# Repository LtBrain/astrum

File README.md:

# **ASTRUM**
  
Astrum is a full robot designed for Science Olympiad's Robot Tour Event (2025-2026). It is designed to follow a predetermined path to navigate a maze and manipulate a water bottle to specific points on the floor. It is equipped with dual GA25 motors, a controller board (Aero), wheel encoders and an IMU to keep track of orientation. These features allow Astrum to quickly navigate the predetermined path efficiently and accurately with a PID loop controlling robot turning and motor speed.  
<br><br>
Astrum was created for the purpose of "placing" at the Mid-Hudson Valley Regionals competition, and to secure Nanuet a medal. Additionally, it serves as an educational tool for other students interested in robotics and control systems. It is able to be programmed in C, as well as Arduino, making it very effective for learning embedded software. This is also practice for myself, testing my design skills with both the hardware, and efficiently programming software to run on said board.  
  
## PCB

## Wiring Diagram 

## BOM
Here's the BOM:  

 |Item #|Name                                       |Link                                     |Amount               |Cost   |
|------|-------------------------------------------|-----------------------------------------|---------------------|-------|
|1     |PCB + Assembly + Shipping                  |jlcpcb.com                               |1 order (2 boards)   |$170.40|
|2     |25GA-370 Brushed Motors                    |https://www.aliexpress.us/item/3256807346702379.html?|2                    |$12.94 |
|3     |Alinan AS5600 Encoder Boards               |https://www.aliexpress.us/item/3256809413529733.html?                              |1 pack (5 Encoders)  |$6.09 |
|4     |STEMMA QT to Male Header Cable             |https://www.aliexpress.com/item/3256805529535394.html?    |2                    |$2.78 |
|5     |2800 mAh AA NIMH Batteries                 |https://www.aliexpress.com/item/3256808440628751.html?                     |1 pack (12 Batteries)|$7.67 |
|6     |4 x AA Battery Holder                      |https://www.aliexpress.com/item/2255799895517935.html?     |2                    |$1.90  |
|7     |M3 16mm SHCS                               |M3 SHCS link                             |50                   |Paid by me  |
|8     |BaneBots T6 Wheel, 2-3/8" x 0.6", Hub Mount|https://banebots.com/t61p-242bp/         |2                    |$6.60  |
|9     |MF128ZZ Bearings - 8mm x 12mm x 3.5mm      |https://www.aliexpress.com/item/3256807566213882.html?                      |1 pack (8 bearings) |$6.10  |
|10    |Polulu 1/2 Inch Metal Ball Caster Wheels   |https://www.aliexpress.com/item/3256808387820251.html?     |4                    |$4.63 |
|11    |Pin Headers                                |https://www.aliexpress.com/item/2255800801798474.html?    |10                    |$1.69  |
|      |                                           |                                         |                     |Total: |
|      |                                           |                                         |                     |$220.80|
 
https://github.com/LtBrain/astrum/blob/main/Astrum%20BOM%20-%20Sheet1.csv

This covers the total sum of all the major parts.  

There is a more in depth BOM for the PCB assembly components itself: [BOM-astrum-JLCPCB Assembly Order.xls](https://github.com/user-attachments/files/23870804/BOM-astrum-JLCPCB.Assembly.Order.xls)  
  
REVIEWERS: Do note that I am aware of the high PCB fabrication costs + shipping, but this is the cheapest I could find it for (at JLCPCB). Additionally, the global standard direct shipping option will not work for this board. Sadly, JLCPCB requires the purchase to be under 59.99 dollars, which this board exceeds. This is why it got so expensive. Also do note that I have optimized my BOMs to be as cheap as possible to lower the amount of money spent by Hackclub.

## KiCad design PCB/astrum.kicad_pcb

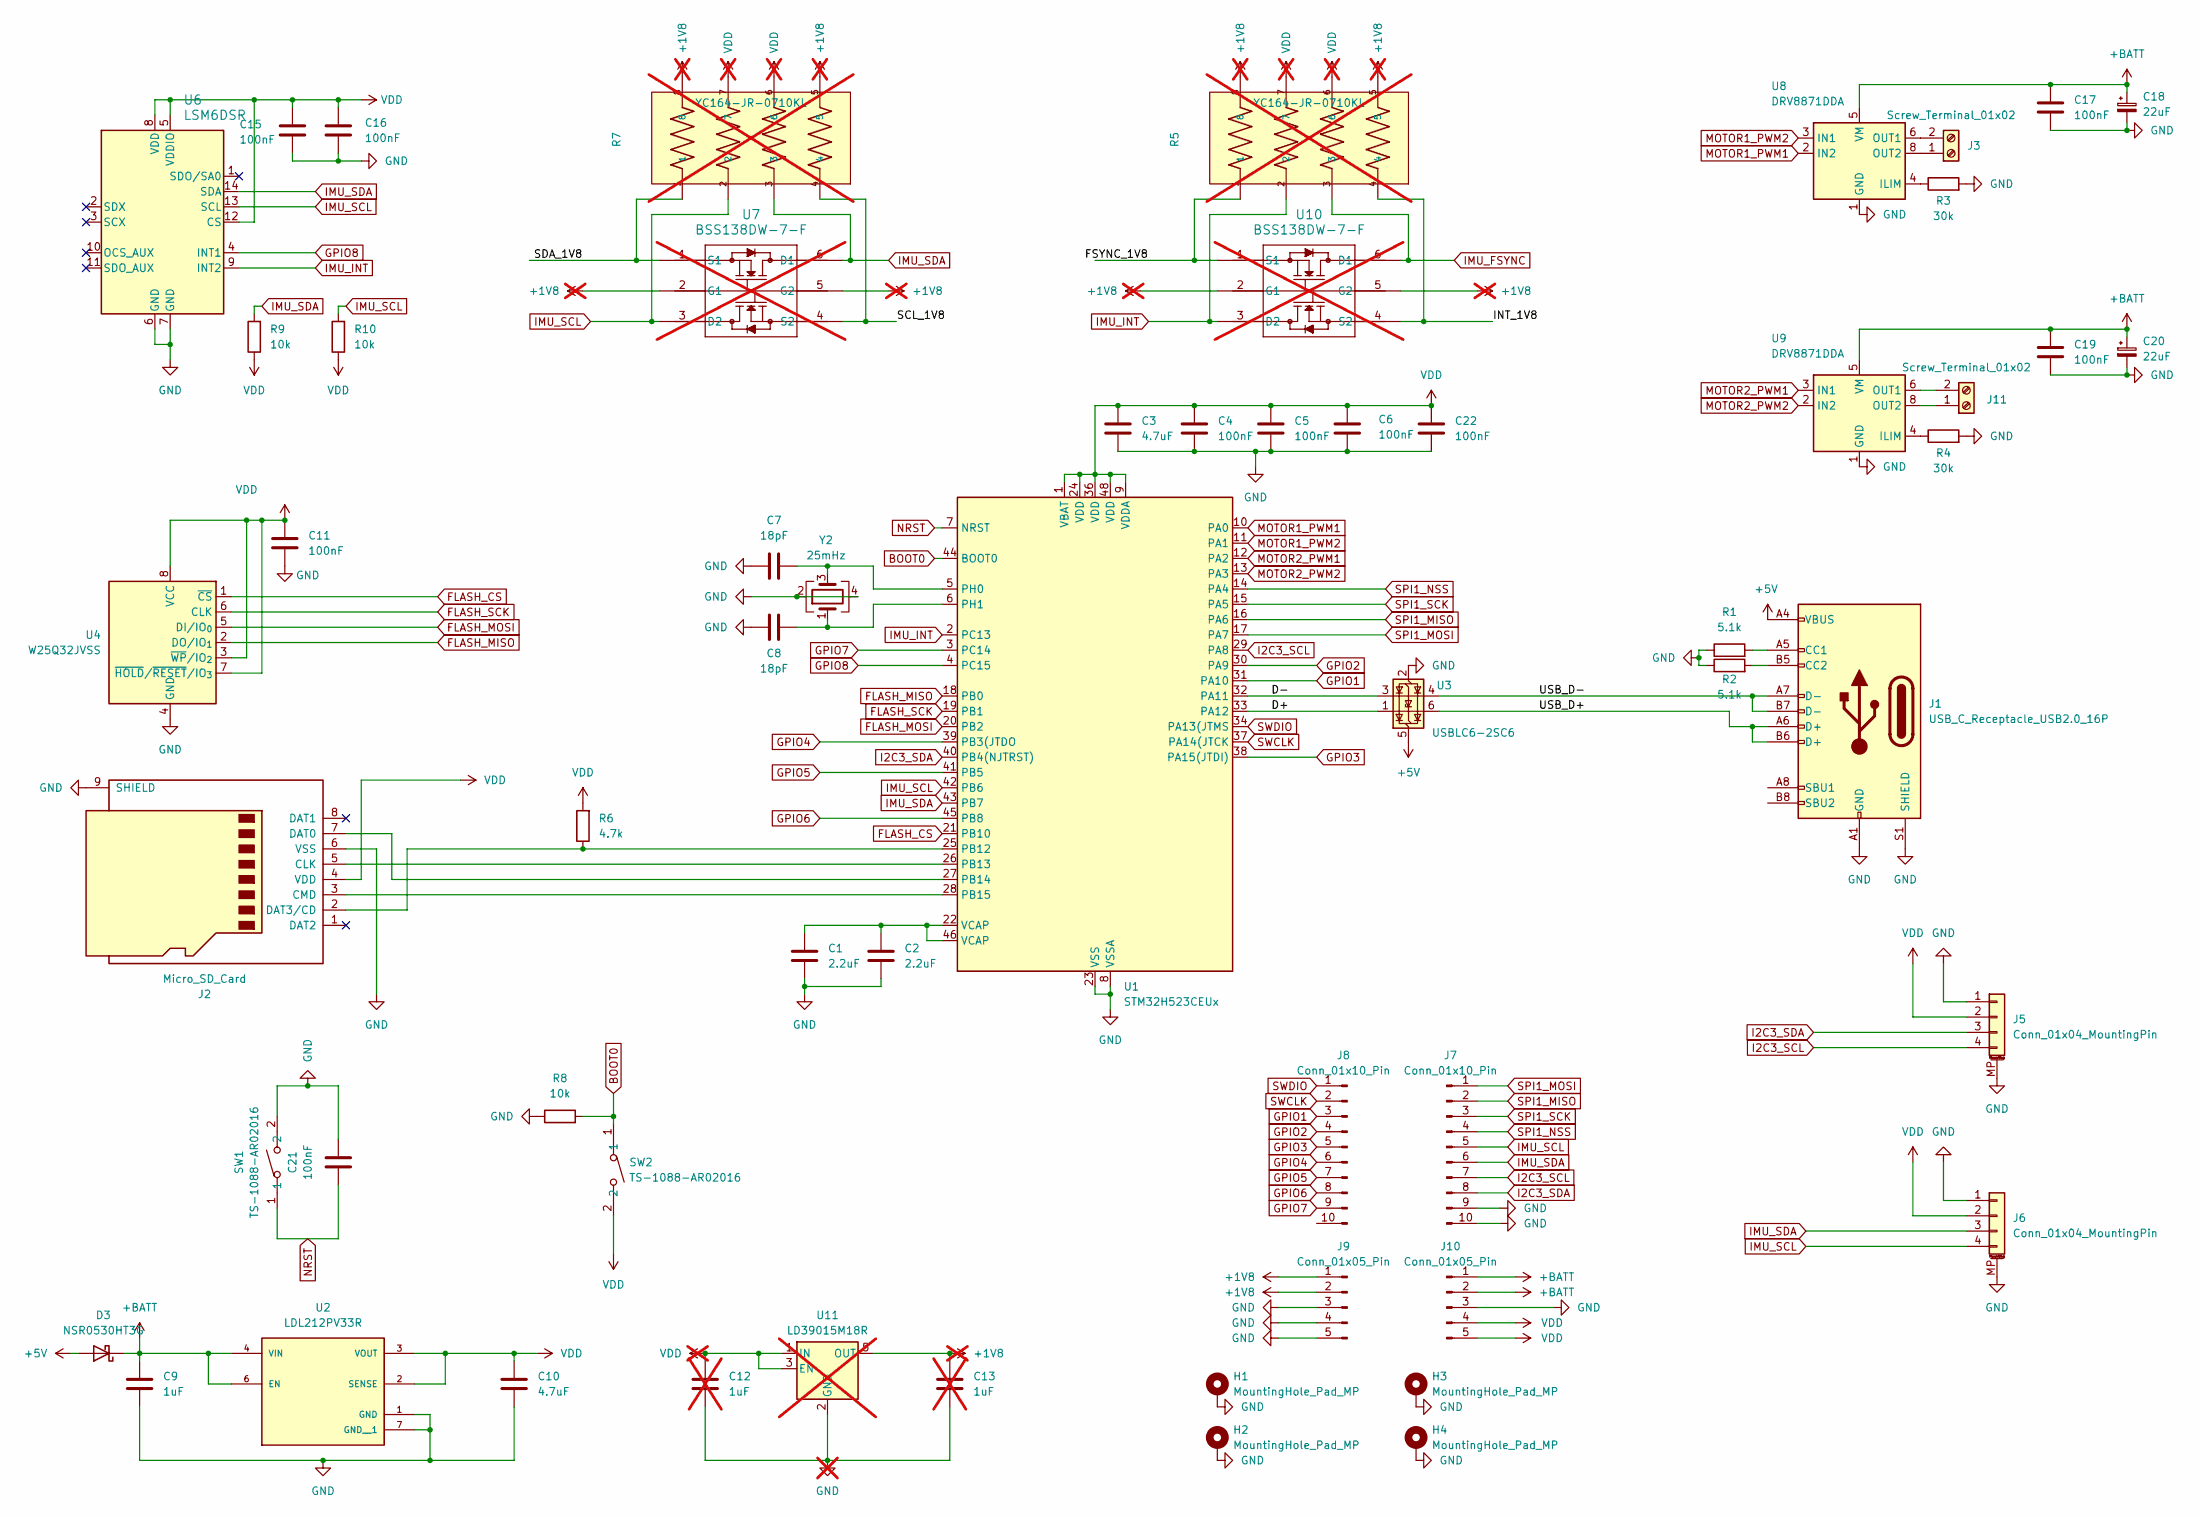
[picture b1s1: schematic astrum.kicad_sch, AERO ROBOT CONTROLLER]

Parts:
C1: 2.2uF; C_0603_1608Metric
C2: 2.2uF; C_0402_1005Metric
C3, C10: 4.7uF; C_0603_1608Metric
C4, C5, C6, C11, C15, C16, C17, C19, C21: 100nF; C_0603_1608Metric
C7, C8: 18pF; C_0603_1608Metric
C9: 1uF; C_0603_1608Metric
C12, C13: 1uF; C_0603_1608Metric; not fitted
C18, C20: 22uF; CP_Elec_4x5.4
C22: 100nF; C_0402_1005Metric
D3: NSR0530HT3G; D_SOD-323
H1, H2, H3, H4: MountingHole_Pad_MP; MountingHole_2.2mm_M2_ISO7380_Pad
J1: USB_C_Receptacle_USB2.0_16P; USB_C_Receptacle_JAE_DX07S016JA1R1500
J2: Micro_SD_Card; microSD_HC_Wuerth_693072010801
J3, J11: Screw_Terminal_01x02; TerminalBlock_bornier-2_P5.08mm
J5, J6: Conn_01x04_MountingPin; JST_SH_SM04B-SRSS-TB_1x04-1MP_P1.00mm_Horizontal
J7, J8: Conn_01x10_Pin; PinHeader_1x10_P2.54mm_Vertical
J9, J10: Conn_01x05_Pin; PinHeader_1x05_P2.54mm_Vertical
R1, R2: 5.1k; R_0603_1608Metric
R3, R4: 30k; R_0603_1608Metric
R5, R7: YC164-JR-0710KL; RESCAXE80P320X160X70-8N; PARTREV 9; not fitted
R6: 4.7k; R_0603_1608Metric
R8, R9, R10: 10k; R_0603_1608Metric
SW1, SW2: TS-1088-AR02016; SW-SMD_L3.9-W3.0-P4.45; LCSC Part C720477
U1: STM32H523CEUx; QFN-48-1EP_7x7mm_P0.5mm_EP5.6x5.6mm
U2: LDL212PV33R; DFN_V33R_STM; PARTREV 5
U3: USBLC6-2SC6; SOT-23-6
U4: W25Q32JVSS; SOIC-8_5.3x5.3mm_P1.27mm
U6: LSM6DSR; LGA_M6DSR_STM
U7, U10: BSS138DW-7-F; SOT363_DIO; not fitted
U8, U9: DRV8871DDA; Texas_HTSOP-8-1EP_3.9x4.9mm_P1.27mm_EP2.95x4.9mm_Mask2.4x3.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
U11: LD39015M18R; SOT-23-5; not fitted
Y2: 25mHz; Crystal_SMD_3225-4Pin_3.2x2.5mm

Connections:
+1V8: C13.1, J9.1, J9.2, R5.5, R5.8, R7.5, R7.8, U7.2 (G1), U7.5 (G2), U10.2 (G1), U10.5 (G2), U11.5 (OUT)
+5V: D3.2 (A), J1.A4 (VBUS), J1.A9 (VBUS), J1.B4 (VBUS), J1.B9 (VBUS), U3.5 (VBUS)
+BATT: C9.1, C17.1, C18.1, C19.1, C20.1, D3.1 (K), J10.1, J10.2, U2.4 (VIN), U2.6 (EN), U8.5 (VM), U9.5 (VM)
/D+: U1.33 (PA12), U3.1 (I/O1)
/D-: U1.32 (PA11), U3.3 (I/O2)
/FSYNC_1V8: R5.1, U10.1 (S1)
/INT_1V8: R5.4, U10.4 (S2)
/SCL_1V8: R7.4, U7.4 (S2)
/SDA_1V8: R7.1, U7.1 (S1)
/USB_D+: J1.A6 (D+), J1.B6 (D+), U3.6 (I/O1)
/USB_D-: J1.A7 (D-), J1.B7 (D-), U3.4 (I/O2)
BOOT0: R8.2, SW2.1, U1.44 (BOOT0)
FLASH_CS: U1.21 (PB10), U4.1 (~CS)
FLASH_MISO: U1.18 (PB0), U4.2 (DO/IO_{1})
FLASH_MOSI: U1.20 (PB2), U4.5 (DI/IO_{0})
FLASH_SCK: U1.19 (PB1), U4.6 (CLK)
GND: C1.2, C2.2, C3.2, C4.2, C5.2, C6.2, C7.1, C8.1, C9.2, C10.2, C11.2, C12.2, C13.2, C15.2, C16.2, C17.2, C18.2, C19.2, C20.2, C21.2, C22.2, H1.MP, H2.MP, H3.MP, H4.MP, J1.A1 (GND), J1.A12 (GND), J1.B1 (GND), J1.B12 (GND), J1.S1 (SHIELD), J2.6 (VSS), J2.9 (SHIELD), J5.1, J5.MP (MountPin), J6.1, J6.MP (MountPin), J7.9, J7.10, J9.3, J9.4, J9.5, J10.3, R1.1, R2.1, R3.2, R4.2, R8.1, SW1.2, U1.8 (VSSA), U1.23 (VSS), U1.35 (VSS), U1.47 (VSS), U1.49 (VSS), U2.1 (GND), U2.7 (GND__1), U3.2 (GND), U4.4 (GND), U6.6 (GND), U6.7 (GND), U8.1 (GND), U8.7 (GND), U8.9 (GND), U9.1 (GND), U9.7 (GND), U9.9 (GND), U11.2 (GND), Y2.2, Y2.4
GPIO1: J8.3, U1.31 (PA10)
GPIO2: J8.4, U1.30 (PA9)
GPIO3: J8.5, U1.38 (PA15(JTDI))
GPIO4: J8.6, U1.39 (PB3(JTDO)
GPIO5: J8.7, U1.41 (PB5)
GPIO6: J8.8, U1.45 (PB8)
GPIO7: J8.9, U1.3 (PC14)
GPIO8: U1.4 (PC15), U6.4 (INT1)
I2C3_SCL: J5.4, J7.7, U1.29 (PA8)
I2C3_SDA: J5.3, J7.8, U1.40 (PB4(NJTRST))
IMU_FSYNC: R5.3, U10.6 (D1)
IMU_INT: R5.2, U1.2 (PC13), U6.9 (INT2), U10.3 (D2)
IMU_SCL: J6.4, J7.5, R7.2, R10.2, U1.42 (PB6), U6.13 (SCL), U7.3 (D2)
IMU_SDA: J6.3, J7.6, R7.3, R9.2, U1.43 (PB7), U6.14 (SDA), U7.6 (D1)
MOTOR1_PWM1: U1.10 (PA0), U8.2 (IN2)
MOTOR1_PWM2: U1.11 (PA1), U8.3 (IN1)
MOTOR2_PWM1: U1.12 (PA2), U9.3 (IN1)
MOTOR2_PWM2: U1.13 (PA3), U9.2 (IN2)
NRST: C21.1, SW1.1, U1.7 (NRST)
unnamed: C1.1, C2.1, U1.22 (VCAP), U1.46 (VCAP)
unnamed: J1.A5 (CC1), R1.2
unnamed: J1.B5 (CC2), R2.2
unnamed: J2.5 (CLK), U1.26 (PB13)
unnamed: J2.3 (CMD), U1.28 (PB15)
unnamed: J2.7 (DAT0), U1.27 (PB14)
unnamed: J2.2 (DAT3/CD), R6.1, U1.25 (PB12)
unnamed: J3.1, U8.8 (OUT2)
unnamed: J3.2, U8.6 (OUT1)
unnamed: J11.1, U9.8 (OUT2)
unnamed: J11.2, U9.6 (OUT1)
unnamed: C7.2, U1.5 (PH0), Y2.3
unnamed: C8.2, U1.6 (PH1), Y2.1
unnamed: R3.1, U8.4 (ILIM)
unnamed: R4.1, U9.4 (ILIM)
SPI1_MISO: J7.2, U1.16 (PA6)
SPI1_MOSI: J7.1, U1.17 (PA7)
SPI1_NSS: J7.4, U1.14 (PA4)
SPI1_SCK: J7.3, U1.15 (PA5)
SWCLK: J8.2, U1.37 (PA14(JTCK)
SWDIO: J8.1, U1.34 (PA13(JTMS)
VDD: C3.1, C4.1, C5.1, C6.1, C10.1, C11.1, C12.1, C15.1, C16.1, C22.1, J2.4 (VDD), J5.2, J6.2, J10.4, J10.5, R5.6, R5.7, R6.2, R7.6, R7.7, R9.1, R10.1, SW2.2, U1.1 (VBAT), U1.9 (VDDA), U1.24 (VDD), U1.36 (VDD), U1.48 (VDD), U2.2 (SENSE), U2.3 (VOUT), U4.3 (~WP/IO_{2}), U4.7 (~HOLD/~RESET/IO_{3}), U4.8 (VCC), U6.5 (VDDIO), U6.8 (VDD), U6.12 (CS), U11.1 (IN), U11.3 (EN)

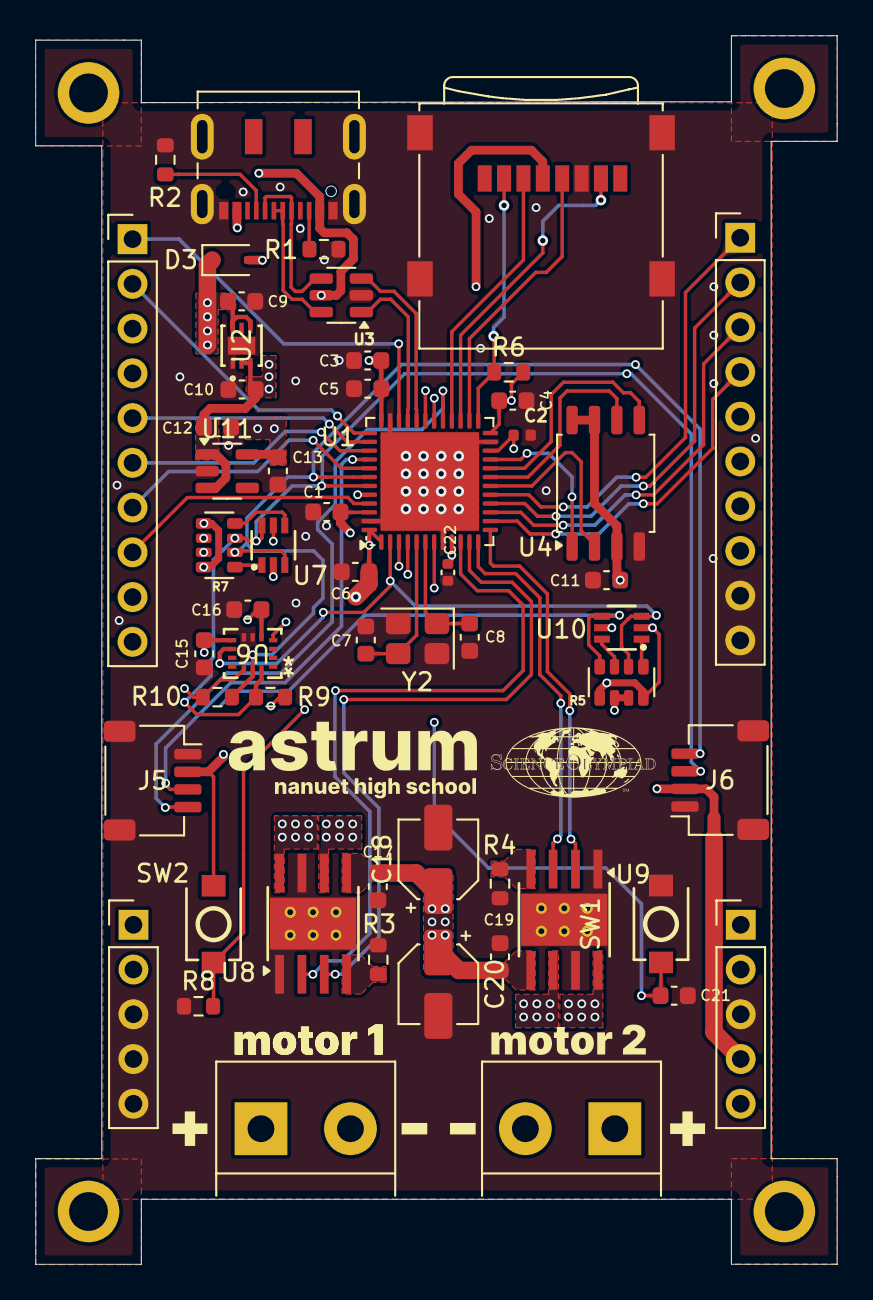
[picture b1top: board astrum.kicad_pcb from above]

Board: 4 copper layers, 45.5 x 69.7 mm, 59 parts (0 on the bottom side), 58 nets.

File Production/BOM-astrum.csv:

Comment,Designator,Footprint,LCSC,Quantity
100nF,"C11,C15,C16,C17,C19,C21,C4,C5,C6",C_0603_1608Metric,C14663,9
100nF,C22,C_0402_1005Metric,C1525,1
10k,"R10,R8,R9",R_0603_1608Metric,C25804,3
18pF,"C7,C8",C_0603_1608Metric,C1647,2
1uF,"C12,C13,C9",C_0603_1608Metric,C15849,3
2.2uF,C2,C_0402_1005Metric,C12530,1
2.2uF,C1,C_0603_1608Metric,C23630,1
22uF,"C18,C20",CP_Elec_4x5.4,C3356,2
25mHz,Y2,Crystal_SMD_3225-4Pin_3.2x2.5mm,C9006,1
30k,"R3,R4",R_0603_1608Metric,C22984,2
4.7k,R6,R_0603_1608Metric,C23162,1
4.7uF,"C10,C3",C_0603_1608Metric,C19666,2
5.1k,"R1,R2",R_0603_1608Metric,C23186,2
Conn_01x04_MountingPin,"J5,J6",JST_SH_SM04B-SRSS-TB_1x04-1MP_P1.00mm_Horizontal,C160404,2
DRV8871DDA,"U8,U9",Texas_HTSOP-8-1EP_3.9x4.9mm_P1.27mm_EP2.95x4.9mm_Mask2.4x3.1mm_ThermalVias,C75864,2
LDL212PV33R,U2,DFN_V33R_STM,C2969892,1
LSM6DSR,U6,LGA_M6DSR_STM,C784817,1
Micro_SD_Card,J2,microSD_HC_Wuerth_693072010801,C5912397,1
NSR0530HT3G,D3,D_SOD-323,C191023,1
STM32H523CEUx,U1,QFN-48-1EP_7x7mm_P0.5mm_EP5.6x5.6mm,C26082147,1
TS-1088-AR02016,"SW1,SW2",SW-SMD_L3.9-W3.0-P4.45,C720477,2
USBLC6-2SC6,U3,SOT-23-6,C7519,1
USB_C_Receptacle_USB2.0_16P,J1,USB_C_Receptacle_JAE_DX07S016JA1R1500,C3197885,1
W25Q32JVSS,U4,SOIC-8_5.3x5.3mm_P1.27mm,C97521,1
Conn_01x10_Pin,J8,PinHeader_1x10_P2.54mm_Vertical,,1
Conn_01x10_Pin,J7,PinHeader_1x10_P2.54mm_Vertical,,1
Conn_01x05_Pin,J10,PinHeader_1x05_P2.54mm_Vertical,,1
Screw_Terminal_01x02,J11,TerminalBlock_bornier-2_P5.08mm,,1
Screw_Terminal_01x02,J3,TerminalBlock_bornier-2_P5.08mm,,1
Conn_01x05_Pin,J9,PinHeader_1x05_P2.54mm_Vertical,,1

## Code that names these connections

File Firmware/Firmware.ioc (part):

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Mcu.Name=STM32H523CEUx
Mcu.Package=UFQFPN48
Mcu.UserName=STM32H523CEUx
PA0.Signal=S_TIM2_CH1
PA1.Signal=S_TIM2_CH2
PA11.Mode=Device
PA11.Signal=USB_DM
PA12.Mode=Device
PA12.Signal=USB_DP
PA13(JTMS/SWDIO).Mode=Serial_Wire
PA13(JTMS/SWDIO).Signal=DEBUG_JTMS-SWDIO
PA14(JTCK/SWCLK).Mode=Serial_Wire
PA14(JTCK/SWCLK).Signal=DEBUG_JTCK-SWCLK
PA2.Signal=S_TIM2_CH3
PA3.Signal=S_TIM2_CH4
PA4.Signal=SPI1_NSS
PA5.Signal=SPI1_SCK
PA6.Signal=SPI1_MISO
PA7.Signal=SPI1_MOSI
PA8.Mode=I2C
PA8.Signal=I2C3_SCL
PB0.Mode=Full_Duplex_Master
PB0.Signal=SPI3_MISO
PB1.Mode=Full_Duplex_Master
PB1.Signal=SPI3_SCK
PB10.Signal=GPIO_Output
PB12.Mode=NSS_Signal_Hard_Output
PB12.Signal=SPI2_NSS
PB13.Mode=Full_Duplex_Master
PB13.Signal=SPI2_SCK
PB14.Mode=Full_Duplex_Master
PB14.Signal=SPI2_MISO
PB15.Mode=Full_Duplex_Master
PB15.Signal=SPI2_MOSI
PB2.Mode=Full_Duplex_Master
PB2.Signal=SPI3_MOSI
PB4(NJTRST).Mode=I2C
PB4(NJTRST).Signal=I2C3_SDA
PB6.Mode=I2C
PB6.Signal=I2C1_SCL
PB7.Mode=I2C
PB7.Signal=I2C1_SDA
PC13.Signal=GPIO_Input
PH0-OSC_IN(PH0).Mode=HSE-External-Oscillator
PH0-OSC_IN(PH0).Signal=RCC_OSC_IN
PH1-OSC_OUT(PH1).Mode=HSE-External-Oscillator
PH1-OSC_OUT(PH1).Signal=RCC_OSC_OUT
RCC.HSE_VALUE=25000000
RCC.SYSCLKFreq_VALUE=250000000
RCC.SYSCLKSource=RCC_SYSCLKSOURCE_PLLCLK
board=custom

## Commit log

2025-10-12 add stm32, basic peripherals
2025-10-12 add drv8871 drivers to the board
2025-10-12 add imu schematics
2025-10-13 route the processing side of the board
2025-10-14 add the drv routing and header pins + power supply
2025-10-17 add more gpio header things
2025-10-17 fix the power plane and the mounting holes
2025-11-06 add firmware and cad stuff
2025-11-08 generate the cubemx project, add as5600 driver code
2025-11-09 add icm20948 driver
2025-11-09 add drv8871 motor helper?
2025-11-10 add PID controller
2025-11-11 some more pid?
2025-11-19 production commit
2025-11-19 Add project title and image to README
2025-11-19 Add description of Astrum robot for Science Olympiad
    Added a brief description of the Astrum robot's purpose and functionality.
2025-11-19 Enhance README with detailed robot description
    Expanded project description to include technical specifications and educational purpose.
2025-12-01 update production files
2025-12-02 actually push the bom
2025-12-02 update bom to include new 1v8 regulator
2025-12-02 Add BOM section with links to detailed resources
    Added a Bill of Materials (BOM) section to the README.
2025-12-02 Revise BOM section with item details and links
    Updated the BOM section with detailed item list and links.
2025-12-02 add production step files
2025-12-03 final production files?
2025-12-05 Revise BOM with new links and updated prices
    Updated links and costs for various components in the bill of materials.
2025-12-05 Revise Astrum BOM with new links and prices
    Updated item details and costs in the BOM.
2025-12-05 Update Astrum BOM with new item formatting
2025-12-06 Update README with PCB costs and BOM details
    Added notes regarding PCB fabrication costs and BOM optimization.
2025-12-14 make the board cheaper?
2025-12-14 fix oscillator
2025-12-14 Update BOM with shipping costs and total amount
2025-12-14 Revise BOM with updated costs and shipping
    Updated item costs and added shipping to PCB assembly.
2026-01-16 fix some dum vcap thingies
2026-01-24 update stuff again
